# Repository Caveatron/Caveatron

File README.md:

# Caveatron

The Caveatron is a unique compact, handheld, electronic device for mapping caves or other underground environments. It functions as a cave survey tool, recording conventional distance, azimuth and inclination measurements and can also go far beyond that with its integrated LIDAR to capture a full 3D scan of the cave interior. It greatly speeds up the cave survey process by recording station-to-station shots in just a few seconds and performs a station-to-station 3D scan traverse in less than a minute. The user can fully interact with the device and review data with the built-in touchscreen. A USB port provides access to the stored data from a PC or Mac and is also used to charge the integrated long-life battery pack. The station measurement file is compatible with Walls Cave Mapping Software and the LIDAR scan file can be quickly processed into a standard point cloud with custom-written software. The Caveatron is designed to be easily portable, lightweight, and low cost as well as water and dirt resistant and durable enough to survive regular use in a cave.

## Key Features

- Survey and 3D scan caves
- 12 m or 30 m LIDAR range at up to 32000 pts/sec
- Laser rangefinder up to 40 m
- Integrated intertial measurement unit including digital compass, inclinometer, and gyroscope
- Position estimation during scanning
- Fast Teensy processor
- File transfer to PC over USB
- Water/dust resistant 3D printed enclosure
- Custom printed circuit board

## What's New (2024-05-03)

Rev C is the current and preferred version and is the only one in active development. This version uses the faster Teensy 4.1 processor and has several enhancements including ability to use the 30m RPLIDAR S2 or 12 RPLIDAR A1M8, a new magnetometer module for much improved compass accuracy and reliability, a capacitive touchscreen, faster battery charging, and a smaller size.
New revisions of the Rev C board (C.3 and C.4) have been posted along with an updated bill of materials. The Rev C assembly documentation has not yet been updated for the new PCBs but is not significantly different.

Rev B is based on the older Teensy 3.6 processor and is now deprecated and some components may no longer be available.

The original, Arduino Due-based version (Rev A) information is all still available and can now be found in the legacy_material_rev-A directory.
In the Rev A version, many people had difficulty with compiling the code in terms of getting all the libraries to work together and getting all the settings right. With the Teensy, it is relatively easy to load a pre-compiled HEX file, avoiding all the software headaches. For now I am just going to provide the HEX file instead of all the code to simplify things, since the code has gotten even more complex in the new version and I am no longer using the Arduino IDE. If you want to work on the code, please contact me directly.

## Summary of Caveatron Directory Contents for each Revision

### Documentation
- Bill of Materials
- Assembly Instructions
- Wire Harness Assembly Instructions
- 3D Printed Parts Description

### PCB
- Schematic diagram
- KiCad files
- PCB gerber files

### Mechanical
- STL files for all 3D printed parts
- STEP files for all 3D printed parts

## These items can be found in other folders:

### Calibration
Info and calculators can be found at https://github.com/Caveatron/Calibration

### Software
Software can be found at https://github.com/Caveatron/Software

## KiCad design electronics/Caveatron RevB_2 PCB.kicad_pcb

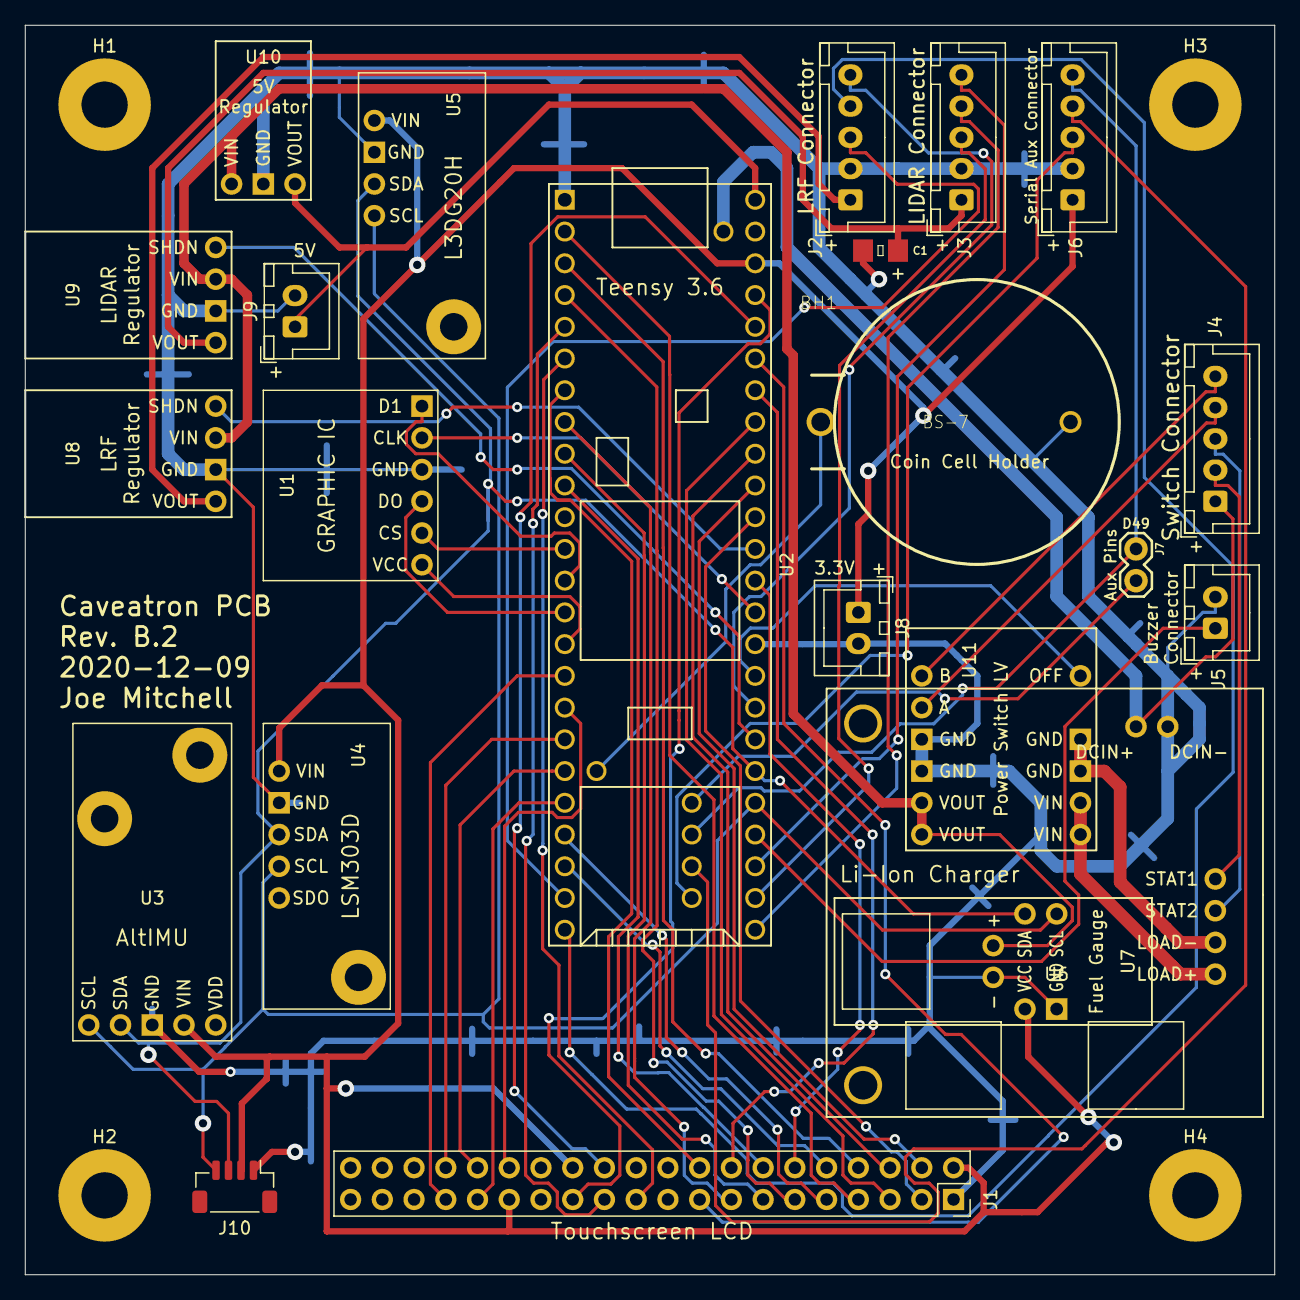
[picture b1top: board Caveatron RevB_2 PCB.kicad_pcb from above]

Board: 2 copper layers, 100.0 x 100.0 mm, 27 parts (0 on the bottom side), 60 nets.

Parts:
BH1: BS-7
C1: CP1; 1206
H1, H2, H3, H4: MountingHole_3.7mm_Pad
J1: Conn_02x20_Odd_Even; 2x20_P2.54mm_BuyDisplay_LCD_Socket_Header
J2, J3, J4, J6: CONN_05JST; JST_XH_B5B-XH-A_1x05_P2.50mm_Vertical
J5, J8, J9: CONN_02JST-PTH-2; JST_XH_B2B-XH-A_1x02_P2.50mm_Vertical
J7: Conn_01x02_Female; 1X02
J10: QWIIC_CONNECTOR (VERTICAL); JST_SH_BM04B-SRSS-TB_1x04-1MP_P1.00mm_Vertical
U1: FONT_IC
U2: Teensy3.6; Teensy36-S
U3: AltIMU; AltIMU-S
U4: LSM303D; LSM303D-S
U5: L3GD20H; L3GD20H-S
U6: Batt_Charger; Adafruit_Li-Ion_Charger-S
U7: Fuel_Gauge; Fuel_Gauge-S
U8, U9: Pololu_Adj_Reg
U10: Pololu_5V_Reg
U11: Power_Switch; Pololu_Pwr_Switch-S

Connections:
/3V3: J1.2, J1.26, J1.29, J6.1, J8.1, J10.2, U2.51, U3.4, U4.2, U5.2, U7.3
/5V: J9.1, U2.53, U10.3
/BATT+: U6.3, U11.1, U11.3
/BATT-: U6.4, U11.5, U11.7
/BUZZER: J5.1, U2.33
/D49: J6.5, J7.1, U2.78
/D50: J7.2, U2.79
/DB0: J1.3, U2.43
/DB1: J1.4, U2.44
/DB2: J1.5, U2.46
/DB3: J1.6, U2.45
/DB4: J1.7, U2.2
/DB5: J1.8, U2.3
/DB6: J1.9, U2.21
/DB7: J1.10, U2.22
/DB8: J1.11, U2.4
/DB9: J1.12, U2.41
/DB10: J1.13, U2.9
/DB11: J1.14, U2.10
/DB12: J1.15, U2.8
/DB13: J1.16, U2.47
/DB14: J1.17, U2.48
/DB15: J1.18, U2.7
/GND: BH1.NEG, C1.2, J1.1, J2.2, J3.2, J5.2, J6.2, J8.2, J9.2, J10.1, U1.3, U2.1, U2.39, U3.3, U4.3, U5.3, U6.2, U7.2, U7.4, U8.2, U9.2, U10.2, U11.6, U11.8
/LIDAR_PWM: J3.5, U2.32
/LIDAR_PWR: U2.36, U9.4
/LIDAR_RX: J3.3, U2.31
/LIDAR_TX: J3.4, U2.30
/LRF_PWR: U2.42, U8.4
/LRF_RST: J2.5, U2.37
/LRF_RX: J2.3, U2.23
/LRF_TX: J2.4, U2.24
/L_CS: J1.23, U2.5
/RS: J1.25, U2.50
/RSET: J1.21, U2.6
/RTC_BATT: BH1.POS, U2.25
/RX6: J6.3, U2.76
/SCL: J10.4, U2.34, U3.1, U4.5, U5.5, U7.7
/SDA: J10.3, U2.35, U3.2, U4.4, U5.4, U7.6
/SYS_OFF: U2.38, U11.11
/TCLK: J1.33, U2.16
/TDIN: J1.34, U2.18
/TDOUT: J1.32, U2.19
/TIRQ: J1.31, U2.20
/TX6: J6.4, U2.77
/T_CS: J1.30, U2.17
/V_USB: J4.1, U2.54, U6.1
/WR: J1.24, U2.49
unnamed: C1.1, J3.1, U9.1
unnamed: J2.1, U8.1
unnamed: J4.2, U6.6
unnamed: J4.3, U6.5
unnamed: J4.4, U11.10
unnamed: J4.5, U11.12
unnamed: U1.1, U2.13
unnamed: U1.2, U2.40
unnamed: U1.4, U2.14
unnamed: U1.5, U2.12
unnamed: U1.6, U2.15
unnamed: U7.1, U8.3, U9.3, U10.1, U11.2, U11.4

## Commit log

2018-01-16 uncomment eigen stuff
2018-01-27 Fixed several serious bugs in user calibration routine
2018-01-27 Added release notes
2018-02-08 Version number and date corrections
2018-03-05 Release Version 1.0 of the Caveatron Firmware
    Initial release of Caveatron firmware
    Initial release of calibration parameter uploader and downloader
2018-05-05 Add a couple of casts to silence compilation warnings
2018-05-05 Fix download URL for ColdTears library in README
2018-08-01 Update Caveatron software to version 1.10
    v1.10 adds several new features, the most signficant of which is that you can now review LIDAR data from a completed scan.
    - Added "View LIDAR Scans" function to view list of LIDAR scans in the current survey and basic information about them. Scans are displayed in order from newest to oldest.
    - Added function to select any completed LIDAR scan data in the current survey and view it on screen. A plan or profile view can be chosen and a 2D plot of the data in a horizontal or vertical slice 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
2018-12-16 Incorporates RP LIDAR modules, adds calibration checker, and bugfixes
2018-12-16 Updated release notes for Caveatron 1.20
2019-02-09 Libraries Update for Caveatron 1.3
    Updated to add future support of Teensy 3.5/3.6
2019-02-09 Libraries Update for Caveatron 1.3 - REQUIRED!
    Update to support new functions in Caveatron 1.3
2019-02-09 Adds back-sights, shot code selection screen, better scan error handling, and bugfixes
2019-02-27 Fix to v.1.3 that caused year values to be incorrect
2019-03-20 Update to 1.31 - fixes bugs that can cause system freezes
2019-11-07 Updated Caveatron_Hardware library for firmware 1.4
2019-11-07 Update with new calibration loading & saving method plus several improvements & bug fixes
    Change Notes(1.40):
    CRITICAL: You must update the Caveatron_Hardware library to v1.4.
    When creating a new survey, calibration parameters are now stored in a .IMU file
    Added ability to load and save calibration parameters from/to a file on the SD card (use of Caveatron_Downloader/Uploader sketch no longer required).
    Added compatibility with Caveatron Connect 1.1 to provide for transfer of .IMU calibration files from a PC to the Caveatron SD card.
    Added magnetometer alignment to the View IMU Calibration screen
2020-01-26 New Caveatron Version - Rev B
    Reorganize repository and add information on Caveatron Rev B. Previous Rev A Caveatron info moved to new caveatron_rev-A_version repository.
2020-01-29 Added 3D parts description document
2020-01-30 Firmware file updated with instructions
2020-02-19 Minor BOM revisions and addition
2020-02-21 Add drawings of LRF and LIDAR windows + BOM revision
2020-03-05 Instructions and Spreadsheets for Setup and Initial Calibration
2020-03-05 Font & Graphics File for SPI Flash IC
2020-03-05 Caveatron Setup Firmware v1
2020-03-05 Fonts & Graphics for SPI Flash - Used with Caveatron_Setup firmware
2020-03-05 Updated READMEs
2020-03-07 New v2.02 with updated calib loading and other fixes
2020-04-06 New Wire Harness Assembly Instruction
2020-04-07 Minor revision to Caveatron Setup firmware
2020-04-07 New Wire Harness Assembly document
2020-04-10 New Assembly Instructions Document
2020-04-10 Updated BOM
2020-04-10 New Assembly Instructions and Updated Readme
2020-04-11 Updated Caveatron_Setup with bug fixes
2020-05-10 Fixed to prevent small LRF tilt
2020-05-10 Add STEP file versions for all 3D printed parts
2020-05-10 Add Fusion360 native versions of all 3D printed parts
2020-05-11 Add KiCad PCB project files
2020-05-29 Fixed minor issue found by Craig Hamer
2020-05-29 Fixed swapped LRF wire found by Dave Jones
2020-06-14 Fixes to LRF in Passage Mode and more
2020-09-09 Adding simple serial uploader and downloader utilities compatible with Rev B
2020-09-17 New Caveatron version 2.04
2020-10-25 Updates for software version 2.05 and new display
2020-10-29 Updated Caveatron_Setup to v1.2
2020-11-03 Modified document
2020-12-10 Revised PCB design for BuyDisplay
2020-12-12 New lid design for BuyDisplay 3.5" LCD module
2020-12-14 Posting of PCB rev B.2 Gerbers
2020-12-18 Updated Parameter Uploader and Downloader to v2.1
2020-12-18 New version of Caveatron Setup adding support for MinIMU-9 v5
2020-12-18 Fixed cell positions in result tab to match IMU file
2020-12-19 New software version 2.10
2021-01-27 Update to fix small bug. Version number unchanged - build date updated to 2021-01
2021-02-02 Moving hosting of PC software from website to Github
2021-02-12 Caveatron Process 2.1 Update
2021-02-28 Added Kicad files for PCB B2 and renamed others
2021-03-25 Updated BOM with new links and corrections
2021-04-27 Site Reorganization
2021-04-29 Added Rev B3 PCB design files
2021-04-29 Updated Caveatron User Guide
2021-08-03 New version of RPLIDAR lid and 3D printed parts document
2022-09-22 Add Rev C folder
2022-11-13 Rev C enclosure 3D print files
2022-12-10 Added Rev C STEP files
2023-01-13 Added documentation
2023-01-13 Updated files
2023-01-27 Updated Assembly Instructions
2023-02-06 Minor 3D print file revisions
2023-06-08 Fixed problem in file
2024-01-21 Updated User Guide
2024-05-03 Release of new PCB revisions
2024-05-09 Updated documentation
